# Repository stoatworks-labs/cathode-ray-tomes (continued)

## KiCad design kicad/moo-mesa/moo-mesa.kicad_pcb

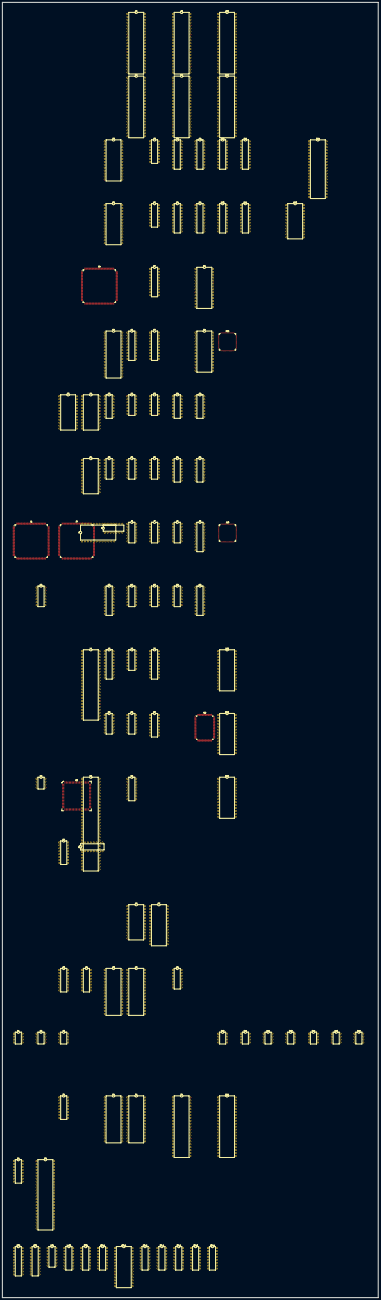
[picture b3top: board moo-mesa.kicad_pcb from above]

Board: 2 copper layers, 326.1 x 1123.8 mm, 109 parts (0 on the bottom side), 698 nets, no tracks yet.

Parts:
A6: HN624116P; DIP-42_W15.24mm
A8, A10: 065A08; DIP-42_W15.24mm
B6: HN624116P; DIP-42_W15.24mm
B8, B10: 065A08; DIP-42_W15.24mm
C5: HM62256BLP; DIP-28_W15.24mm
C7: 74LS157; DIP-16_W7.62mm
C8, C9, C10, C11: 74LS374; DIP-20_W7.62mm
C14: Z80CPU; DIP-40_W15.24mm
D5: MB8464A-10W-15W; DIP-28_W15.24mm
D7: 74LS174; DIP-16_W7.62mm
D8, D9, D10, D11: 74LS374; DIP-20_W7.62mm
D13: YM2151; DIP-24_W15.24mm
E4: 054539; PQFP-160_28x28mm_P0.65mm
E7: PAL16L8; DIP-20_W7.62mm
E9: LH5168D-80L; DIP-28_W15.24mm
F5: 27C020; DIP-32_W15.24mm
F6, F7: 74LS245; DIP-20_W7.62mm
F9: LH5168D-80L; DIP-28_W15.24mm
F10: 053246; TQFP-120_14x14mm_P0.4mm
G3: 051550; DIP-24_W15.24mm
G4: HM6116P-3; DIP-24_W15.24mm
G5: 74LS367; DIP-16_W7.62mm
G6: 74LS04; DIP-14_W7.62mm
G6B, G7B: 74LS245; DIP-20_W7.62mm
G7: 74LS08; DIP-14_W7.62mm
G8, G9: 74LS157; DIP-16_W7.62mm
H4: HM6116P-3; DIP-24_W15.24mm
H5: 74LS21; DIP-14_W7.62mm
H6: 74LS08; DIP-14_W7.62mm
H7: 74LS32; DIP-14_W7.62mm
H8, H9: 74LS157; DIP-16_W7.62mm
J1: 054157; PQFP-160_28x28mm_P0.65mm
J3: 054338; PQFP-160_28x28mm_P0.65mm
J4: HM6116P-3; DIP-24_W15.24mm
J5: 74LS07; DIP-14_W7.62mm
J6: 74LS74; DIP-14_W7.62mm
J7: 74LS32; DIP-14_W7.62mm
J8: 74LS86; DIP-14_W7.62mm
J9: 74LS273; DIP-20_W7.62mm
J10: 053247; TQFP-120_14x14mm_P0.4mm
K2, K8: 74LS04; DIP-14_W7.62mm
K5, K9: 74LS273; DIP-20_W7.62mm
K6: 74LS32; DIP-14_W7.62mm
K7: 74LS74; DIP-14_W7.62mm
L4: DIP-48_W15.24mm
L5, L7: 74LS273; DIP-20_W7.62mm
L6: 74LS04; DIP-14_W7.62mm
L6B: 74LS138; DIP-14_W7.62mm
L10: MB8464A-10W-15W; DIP-28_W15.24mm
L_B6: 74LS157; DIP-16_W7.62mm
M5, M6: 74LS04; DIP-14_W7.62mm
M6B: 74LS138; DIP-16_W7.62mm
M7: 74LS174; DIP-16_W7.62mm
M9: 053251; PQFP-100_14x20mm_P0.65mm
M10: MB8464A-10W-15W; DIP-28_W15.24mm
N2: ER5911; DIP-8_W7.62mm
N3: MC68000FN; PLCC-68
N4: DIP-64_W15.24mm
N6: 74LS175; DIP-16_W7.62mm
N10: MB8464A-10W-15W; DIP-28_W15.24mm
O3, O4: 74LS257; DIP-16_W7.62mm
P6: PAL20L10; DIP-24_W15.24mm
P7: DIP-28_W15.24mm
Q3: 74LS148; DIP-16_W7.62mm
Q4: 74LS174; DIP-16_W7.62mm
Q5, Q6: 27C010; DIP-32_W15.24mm
Q8: 74LS32; DIP-14_W7.62mm
R3_2: 74LS257; DIP-16_W7.62mm
R5_2: HM62256BLP; DIP-28_W15.24mm
S1, S2, S3, S10, S11, S12, S13, S14, S15, S16: KONAMI_005273; DIP-8_W7.62mm
S3_2: 74LS257; DIP-16_W7.62mm
T3: 74LS257; DIP-16_W7.62mm
T5, T6: 27C010; DIP-32_W15.24mm
T8, T10: 065A08; DIP-42_W15.24mm
U1: AD1868R; DIP-16_W7.62mm
U2: 054321; DIP-48_W15.24mm
U7_1, U7_2, U7_3, U7_4: DIP-16_W7.62mm

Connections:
/1.54CLK: E4.28, U1.4, U2.7
/1P_BTN_1: R3_2.2, S1.1, S1.2
/1P_BTN_2: R3_2.5, S1.5, S1.6
/1P_BTN_3: R3_2.11, S10.1, S10.2
/1P_DOWN: O3.14, S3.5, S3.6
/1P_LEFT: O3.2, S2.1, S2.2
/1P_RIGHT: O3.5, S2.5, S2.6
/1P_UP: O3.11, S3.1, S3.2
/2P_BTN_1: R3_2.3, S1.3, S1.4
/2P_BTN_2: R3_2.6, S1.7, S1.8
/2P_BTN_3: R3_2.10, S10.3, S10.4
/2P_DOWN: O3.13, S3.7, S3.8
/2P_LEFT: O3.3, S2.3, S2.4
/2P_RIGHT: O3.6, S2.7, S2.8
/2P_UP: O3.10, S3.3, S3.4
/3P_BTN_1: S11.1, S11.2, T3.2
/3P_BTN_2: S11.5, S11.6, T3.5
/3P_BTN_3: S14.1, S14.2, T3.11
/3P_DOWN: S3_2.14, S13.5, S13.6
/3P_LEFT: S3_2.2, S12.1, S12.2
/3P_RIGHT: S3_2.5, S12.5, S12.6
/3P_START: S14.5, S14.6, T3.14
/3P_UP: S3_2.11, S13.1, S13.2
/4MCLK: D13.24, L4.10
/4P_BTN_1: S11.3, S11.4, T3.3
/4P_BTN_2: S11.7, S11.8, T3.6
/4P_BTN_3: S14.3, S14.4, T3.10
/4P_DOWN: S3_2.13, S13.7, S13.8
/4P_LEFT: S3_2.3, S12.3, S12.4
/4P_RIGHT: S3_2.6, S12.7, S12.8
/4P_START: S14.7, S14.8, T3.13
/4P_UP: S3_2.10, S13.3, S13.4
/ACOL0: J1.149, M9.57
/ACOL1: J1.148, M9.58
/ACOL2: J1.55, M9.59
/ACOL3: J1.56, M9.60
/APAL0: J1.127, M9.61
/APAL1: J1.126, M9.62
/APAL2: J1.125, M9.63
/BCOL0: J1.147, M9.66
/BCOL1: J1.146, M9.67
/BCOL2: J1.57, M9.68
/BCOL3: J1.58, M9.69
/BNK~SCR: J1.64, L6B.11
/BPAL0: J1.122, M9.70
/BPAL1: J1.119, M9.71
/BPAL2: J1.118, M9.72
/BPAL3: J1.117, M9.73
/CI0: J1.154, L7.3
/CI1: J1.153, L7.4
/CI2: J1.51, L7.7
/CI3: J1.52, L7.8
/CI4: J1.143, L7.13
/CI5: J1.142, L7.14
/CI6: J1.141, L7.17
/CI7: J1.138, L7.18
/COIN_1: O4.2, S15.1, S15.2
/COIN_2: O4.5, S15.3, S15.4
/COIN_3: O4.11, S15.5, S15.6
/COIN_4: O4.14, S15.7, S15.8
/COLCS: L6B.14, P7.22
/CRKB: F10.9, N6.3
/CR~CS: J10.9, M6B.13
/DTACK: H5.2, J3.35
/FCOL0: J1.152, L_B6.14
/FCOL1: J1.151, L_B6.11
/FCOL2: J1.53, L_B6.5
/FCOL3: J1.54, L_B6.2
/FPAL0: J1.135, M9.51
/FPAL1: J1.134, M9.52
/FPAL2: J1.133, M9.54
/FPAL3: J1.132, M9.55
/FPAL4: H6.12, J1.137, M9.56
/G5P11: F7.13, G5.11
/G5P13: F7.12, G5.13
/GFXROMA0: T8.10, T10.10
/GFXROMA1: T8.9, T10.9
/GFXROMA2: T8.8, T10.8
/GFXROMA3: T8.7, T10.7
/GFXROMA4: T8.6, T10.6
/GFXROMA5: T8.5, T10.5
/GFXROMA6: T8.4, T10.4
/GFXROMA7: T8.3, T10.3
/GFXROMA8: T8.41, T10.41
/GFXROMA9: T8.40, T10.40
/GFXROMA10: T8.39, T10.39
/GFXROMA11: T8.38, T10.38
/GFXROMA12: T8.37, T10.37
/GFXROMA13: T8.36, T10.36
/GFXROMA14: T8.35, T10.35
/GFXROMA15: T8.34, T10.34
/GFXROMA16: T8.33, T10.33
/GFXROMA17: T8.2, T10.2
/GFXROMA18: T8.1, T10.1
/GFXROMA19: T8.42, T10.42
/GFXROMD0: J1.16, T8.14
/GFXROMD1: J1.17, T8.16
/GFXROMD2: J1.18, T8.18
/GFXROMD3: J1.19, T8.20
/GFXROMD4: J1.9, T8.23
/GFXROMD5: J1.11, T8.25
/GFXROMD6: J1.12, T8.27
/GFXROMD7: J1.13, T8.29
/GFXROMD8: J1.3, T8.15
/GFXROMD9: J1.4, T8.17
/GFXROMD10: J1.5, T8.19
/GFXROMD11: J1.6, T8.21
/GFXROMD12: J1.155, T8.24
/GFXROMD13: J1.156, T8.26
/GFXROMD14: J1.157, T8.28
/GFXROMD15: J1.158, T8.30
/GFXROMD16: J1.44, T10.14
/GFXROMD17: J1.45, T10.16
/GFXROMD18: J1.46, T10.18
/GFXROMD19: J1.47, T10.20
/GFXROMD20: J1.36, T10.23
/GFXROMD21: J1.37, T10.25
/GFXROMD22: J1.38, T10.27
/GFXROMD23: J1.39, T10.29
/GFXROMD24: J1.29, T10.15
/GFXROMD25: J1.31, T10.17
/GFXROMD26: J1.32, T10.19
/GFXROMD27: J1.33, T10.21
/GFXROMD28: J1.23, T10.24
/GFXROMD29: J1.24, T10.26
/GFXROMD30: J1.25, T10.28
/GFXROMD31: J1.26, T10.30
/IOCS: L6B.10, O3.15, R3_2.15, S3_2.15, T3.15
/IOCSB: L6B.9, O4.15
/K051550_CLK: G3.1, N6.11
/LYR_PRIO: J6.12, P6.17
/M16: F10.10, J1.111, J10.10, K5.11, L5.11, M6.8, M9.41, N4.56
/M16B: M6.10, M7.9, N3.15
/MAIN_A1: F7.2, F10.7, G6.1, J1.74, J3.11, J10.7, L4.42, M9.85, N3.32, N4.30, P7.10, Q5.12, Q6.12, R5_2.10, T5.12, T6.12, U2.35
/MAIN_A2: F7.3, F10.6, J1.75, J3.12, J10.6, L4.41, M9.84, N3.33, N4.29, P7.9, Q5.11, Q6.11, R5_2.9, T5.11, T6.11, U2.34
/MAIN_A3: F7.4, J3.13, L4.40, M9.83, N3.34, N4.28, P7.8, Q5.10, Q6.10, R5_2.8, T5.10, T6.10, U2.33
/MAIN_A4: F7.5, J3.14, L4.38, M9.82, N3.35, N4.27, P7.7, Q5.9, Q6.9, R5_2.7, T5.9, T6.9, U2.32
/MAIN_A5: F7.6, J3.15, N3.36, N4.24, P7.6, Q5.8, Q6.8, R5_2.6, T5.8, T6.8
/MAIN_A6: F7.7, J3.16, N3.37, N4.23, Q5.7, Q6.7, R5_2.5, T5.7, T6.7
/MAIN_A7: F7.8, J3.17, N3.38, N4.22, Q5.6, Q6.6, R5_2.4, T5.6, T6.6
/MAIN_A8: F7.9, J3.18, N3.39, N4.21, Q5.5, Q6.5, R5_2.3, T5.5, T6.5
/MAIN_A9: F6.2, J3.19, N3.40, N4.20, Q5.27, Q6.27, R5_2.25, T5.27, T6.27
/MAIN_A10: F6.3, J3.21, N3.41, N4.19, Q5.26, Q6.26, R5_2.24, T5.26, T6.26
/MAIN_A11: F6.4, J3.22, N3.42, N4.17, Q5.23, Q6.23, R5_2.21, T5.23, T6.23
/MAIN_A12: F6.5, J3.23, N3.43, N4.16, Q5.25, Q6.25, R5_2.23, T5.25, T6.25
/MAIN_A13: F6.6, L6B.1, M6B.1, N3.44, N4.15, Q5.4, Q6.4, R5_2.2, T5.4, T6.4
/MAIN_A14: L6B.2, M6B.2, N3.45, N4.14, P6.11, Q5.28, Q6.28, R5_2.26, T5.28, T6.28
/MAIN_A15: M6B.3, N3.46, N4.13, P6.10, Q5.29, Q6.29, R5_2.1, T5.29, T6.29
/MAIN_A16: M5.3, N3.47, N4.12, P6.9, Q5.3, Q6.3, T5.3, T6.3
/MAIN_A17: N3.48, N4.11, P6.8, Q5.2, Q6.2, T5.2, T6.2
/MAIN_A18: N3.49, N4.8, P6.7
/MAIN_A19: N3.50, N4.7, P6.6
/MAIN_A20: N3.51, N4.6, P6.5
/MAIN_A21: N3.53, N4.5, P6.4
/MAIN_A22: N3.54, N4.4, P6.3
/MAIN_A23: N3.55, N4.3, P6.13
/MAIN_D0: G7B.2, J1.76, J3.26, J10.30, L4.13, M9.80, N3.5, N4.31, O3.4, O4.4, P7.11, Q4.3, Q5.13, T5.13, U2.44
/MAIN_D1: G7B.3, J1.77, J3.27, J10.29, L4.14, M9.79, N3.4, N4.32, O3.7, O4.7, P7.12, Q4.4, Q5.14, T5.14, U2.43
/MAIN_D2: G7B.4, J1.78, J3.28, J10.28, L4.15, M9.77, N3.3, N4.33, O3.9, O4.9, P7.13, Q4.6, Q5.15, T5.15, U2.42
/MAIN_D3: G7B.5, J1.79, J3.29, J10.27, L4.16, M9.76, N3.2, N4.35, O3.12, O4.12, P7.15, Q4.11, Q5.17, T5.17, U2.41
/MAIN_D4: G7B.6, J1.82, J3.31, J10.26, L4.18, M9.75, N3.1, N4.36, P7.16, Q4.13, Q5.18, R3_2.4, T5.18, U2.40
/MAIN_D5: G7B.7, J1.83, J3.32, J10.25, L4.19, M9.74, N3.68, N4.37, P7.17, Q4.14, Q5.19, R3_2.7, T5.19, U2.39
/MAIN_D6: G7B.8, J1.84, J3.33, J10.24, L4.20, N3.67, N4.38, P7.18, Q5.20, R3_2.9, T5.20, U2.38
/MAIN_D7: G7B.9, J1.85, J3.34, J10.23, L4.21, N3.66, N4.39, P7.19, Q5.21, R3_2.12, T5.21, U2.37
/MAIN_D8: J1.86, J3.36, J10.22, N3.65, N4.40, N6.4, Q6.13, R5_2.11, S3_2.4, T6.13
/MAIN_D9: J1.87, J3.37, J10.20, N3.64, N4.43, N6.5, Q6.14, R5_2.12, S3_2.7, T6.14
/MAIN_D10: G6B.4, J1.88, J3.38, J10.19, N3.63, N4.44, N6.12, Q6.15, R5_2.13, S3_2.9, T6.15
/MAIN_D11: J1.89, J3.39, J10.18, N3.62, N4.45, N6.13, Q6.17, R5_2.15, S3_2.12, T6.17
/MAIN_D12: G6B.6, J1.91, J3.42, J10.17, N3.61, N4.46, Q6.18, R5_2.16, T3.4, T6.18
/MAIN_D13: G6B.7, J1.92, J3.43, J10.15, N3.60, N4.47, Q6.19, R5_2.17, T3.7, T6.19
/MAIN_D14: G6B.8, J1.93, J3.44, J10.14, N3.59, N4.48, Q6.20, R5_2.18, T3.9, T6.20
/MAIN_D15: J1.94, J3.45, J10.13, N3.58, N4.49, Q6.21, R5_2.19, T3.12, T6.21
/MCLK2: F10.12, J10.12, L6.6
/M~RD: F6.9, G7B.1, J1.95, M6.6, R5_2.22
/OBJDMA: F6.19, F7.19, F10.116, K8.5, Q8.2
/OBJROMA0: A8.10, A10.10, B8.10, B10.10, F10.68
/OBJROMA1: A8.9, A10.9, B8.9, B10.9, F10.69
/OBJROMA2: A8.8, A10.8, B8.8, B10.8, F10.70
/OBJROMA3: A8.7, A10.7, B8.7, B10.7, F10.72
/OBJROMA4: A8.6, A10.6, B8.6, B10.6, F10.73
/OBJROMA5: A8.5, A10.5, B8.5, B10.5, F10.74
/OBJROMA6: A8.4, A10.4, B8.4, B10.4, F10.75
/OBJROMA7: A8.3, A10.3, B8.3, B10.3, F10.77
/OBJROMA8: A8.41, A10.41, B8.41, B10.41, F10.78
/OBJROMA9: A8.40, A10.40, B8.40, B10.40, F10.79
/OBJROMA10: A8.39, A10.39, B8.39, B10.39, F10.80
/OBJROMA11: A8.38, A10.38, B8.38, B10.38, F10.82
/OBJROMA12: A8.37, A10.37, B8.37, B10.37, F10.83
/OBJROMA13: A8.36, A10.36, B8.36, B10.36, F10.84
/OBJROMA14: A8.35, A10.35, B8.35, B10.35, F10.85
/OBJROMA15: A8.34, A10.34, B8.34, B10.34, F10.86
/OBJROMA16: A8.33, A10.33, B8.33, B10.33, F10.87
/OBJROMA17: A8.2, A10.2, B8.2, B10.2, F10.88
/OBJROMA18: A8.1, A10.1, B8.1, B10.1, F10.89
/OBJROMA19: A8.42, A10.42, B8.42, B10.42, F10.90
/OCOL0: J10.32, K9.3
/OCOL1: J10.33, K9.4
/OCOL2: J10.34, K9.7
/OCOL3: J10.35, K9.8
/OCOL4: J10.36, K9.13
/OCOL5: J10.37, K9.14
/OCOL6: J10.38, K9.17
/OCOL7: J10.39, K9.18
/OCOL8: J9.3, J10.40
/OPRI0: J9.4, J10.42
/OPRI1: J9.7, J10.43
/OPRI2: J9.8, J10.44
/OPRI3: J9.13, J10.45
/OPRI4: J9.14, J10.47
/ORAM~WEH: E9.27, H7.11
/ORAM~WEL: F9.27, H7.8
/PAIR~CS: L6B.12, U2.36
/PCM0: E4.34, U2.1
/PCM1: E4.26, U2.2
/PCM2: E4.27, U2.3
/PCU~CS: M6B.9, M9.81
/RAMCS: J3.157, P6.21
/REGCS: J3.158, M6B.10
/REG_WRITE: J7.10, L6B.7
/RES: G3.10, L4.7
/R_A0: A6.30, B6.30, C5.10, E4.132
/R_A1: A6.10, B6.10, C5.9, E4.135
/R_A2: A6.9, B6.9, C5.8, E4.137
/R_A3: A6.8, B6.8, C5.7, E4.141
/R_A4: A6.7, B6.7, C5.6, E4.143
/R_A5: A6.6, B6.6, C5.5, E4.146
/R_A6: A6.5, B6.5, C5.4, E4.148
/R_A7: A6.4, B6.4, C5.3, E4.151
/R_A8: A6.3, B6.3, C5.25, E4.153
/R_A9: A6.41, B6.41, C5.24, E4.157
/R_A10: A6.40, B6.40, C5.21, E4.154
/R_A11: A6.39, B6.39, C5.23, E4.152
/R_A12: A6.38, B6.38, C5.2, E4.149
/R_A13: A6.37, B6.37, C5.26, E4.147
/R_A14: A6.36, B6.36, E4.144
/R_A15: A6.35, B6.35, E4.142
/R_A16: A6.34, B6.34, C5.1, E4.138
/R_A17: A6.33, B6.33, E4.136
/R_A18: A6.2, B6.2, E4.156
/R_A19: A6.1, B6.1, E4.158
/R_A20: A6.42, B6.42, E4.159
/R_D0: A6.14, B6.14, C5.11, E4.128
/R_D1: A6.16, B6.16, C5.12, E4.126
/R_D2: A6.18, B6.18, C5.13, E4.124
/R_D3: A6.20, B6.20, C5.15, E4.122
/R_D4: A6.23, B6.23, C5.16, E4.123
/R_D5: A6.25, B6.25, C5.17, E4.125
/R_D6: A6.27, B6.27, C5.18, E4.127
/R_D7: A6.29, B6.29, C5.19, E4.129
/R/~W: J7.5, K6.5, N3.9
/SCRCS: J1.112, K8.2
/SDON: L6B.13, U2.30
/SERVICE1: S16.1, S16.2
/SHD0: J9.17, J10.48
/SHD1: J9.18, J10.49
/SND~IORQ: C14.20, U2.29
/S~RD: C14.21, D5.22, D13.6, E4.67, E7.2
/S~RST: C14.26, D7.1, D13.3, E4.71, F10.3, J5.1, J5.3, J10.3, N4.59, N6.1, Q4.1
/S~WR: C14.22, D5.27, D13.5, E4.68
/XOBJROMD0: A8.14, D9.3
/XOBJROMD1: A8.16, D9.4
/XOBJROMD2: A8.18, D9.7
/XOBJROMD3: A8.20, D9.8
/XOBJROMD4: A8.23, D9.13
/XOBJROMD5: A8.25, D9.14
/XOBJROMD6: A8.27, D9.17
/XOBJROMD7: A8.29, D9.18
/XOBJROMD8: A8.15, D8.3
/XOBJROMD9: A8.17, D8.4
/XOBJROMD10: A8.19, D8.7
/XOBJROMD11: A8.21, D8.8
/XOBJROMD12: A8.24, D8.13
/XOBJROMD13: A8.26, D8.14
/XOBJROMD14: A8.28, D8.17
/XOBJROMD15: A8.30, D8.18
/XOBJROMD16: B8.14, C9.3
/XOBJROMD17: B8.16, C9.4
/XOBJROMD18: B8.18, C9.7
/XOBJROMD19: B8.20, C9.8
/XOBJROMD20: B8.23, C9.13
/XOBJROMD21: B8.25, C9.14
/XOBJROMD22: B8.27, C9.17
/XOBJROMD23: B8.29, C9.18
/XOBJROMD24: B8.15, C8.3
/XOBJROMD25: B8.17, C8.4
/XOBJROMD26: B8.19, C8.7
/XOBJROMD27: B8.21, C8.8
/XOBJROMD28: B8.24, C8.13
/XOBJROMD29: B8.26, C8.14
/XOBJROMD30: B8.28, C8.17
/XOBJROMD31: B8.30, C8.18
/YOBJROMD0: A10.14, D11.3
/YOBJROMD1: A10.16, D11.4
/YOBJROMD2: A10.18, D11.7
/YOBJROMD3: A10.20, D11.8
/YOBJROMD4: A10.23, D11.13
/YOBJROMD5: A10.25, D11.14
/YOBJROMD6: A10.27, D11.17
/YOBJROMD7: A10.29, D11.18
/YOBJROMD8: A10.15, C11.3
/YOBJROMD9: A10.17, C11.4
/YOBJROMD10: A10.19, C11.7
/YOBJROMD11: A10.21, C11.8
/YOBJROMD12: A10.24, C11.13
/YOBJROMD13: A10.26, C11.14
/YOBJROMD14: A10.28, C11.17
/YOBJROMD15: A10.30, C11.18
/YOBJROMD16: B10.14, D10.3
/YOBJROMD17: B10.16, D10.4
/YOBJROMD18: B10.18, D10.7
/YOBJROMD19: B10.20, D10.8
/YOBJROMD20: B10.23, D10.13
/YOBJROMD21: B10.25, D10.14
/YOBJROMD22: B10.27, D10.17
/YOBJROMD23: B10.29, D10.18
/YOBJROMD24: B10.15, C10.3
/YOBJROMD25: B10.17, C10.4
/YOBJROMD26: B10.19, C10.7
/YOBJROMD27: B10.21, C10.8
/YOBJROMD28: B10.24, C10.13
/YOBJROMD29: B10.26, C10.14
/YOBJROMD30: B10.28, C10.17
/YOBJROMD31: B10.30, C10.18
/colmix/053251/BRIT: H8.5, M9.88
/colmix/053251/COL0: G9.2, M9.19
/colmix/053251/COL1: G9.5, M9.18
/colmix/053251/COL2: G9.11, M9.17
/colmix/053251/COL3: G9.14, M9.16
/colmix/053251/COL4: G8.2, M9.14
/colmix/053251/COL5: G8.5, M9.13
/colmix/053251/COL6: G8.11, M9.12
/colmix/053251/COL7: G8.14, M9.11
/colmix/053251/COL8: H9.2, M9.93
/colmix/053251/COL9: H9.5, M9.92
/colmix/053251/COL10: H9.11, M9.91
/colmix/053251/CRAM~CS: G8.1, G9.1, H8.1, H9.1, K7.9
/colmix/053251/FCOLR0: L_B6.4, M9.47
/colmix/053251/FCOLR1: L_B6.7, M9.48
/colmix/053251/FCOLR2: L_B6.9, M9.49
/colmix/053251/FCOLR3: L_B6.12, M9.50
/colmix/053251/L7P2: G9.3, L7.2
/colmix/053251/L7P5: G9.6, L7.5
/colmix/053251/L7P6: G9.10, L7.6
/colmix/053251/L7P9: G9.13, L7.9
/colmix/053251/L7P12: G8.3, L7.12
/colmix/053251/L7P15: G8.6, L7.15
/colmix/053251/L7P16: G8.10, L7.16
/colmix/053251/L7P19: G8.13, L7.19
/colmix/053251/MCLK2: K7.11, L6.1, L7.11
/colmix/053251/MCOL0: G9.4, L5.3
/colmix/053251/MCOL1: G9.7, L5.4
/colmix/053251/MCOL2: G9.9, L5.7
/colmix/053251/MCOL3: G9.12, L5.8
/colmix/053251/MCOL4: G8.4, L5.13
/colmix/053251/MCOL5: G8.7, L5.14
/colmix/053251/MCOL6: G8.9, L5.17
/colmix/053251/MCOL7: G8.12, L5.18
/colmix/053251/MCOLB0: H6.9, H9.4, K5.3
/colmix/053251/MCOLB1: H9.7, K5.4, L6.9
/colmix/053251/MCOLB2: H9.9, K5.7, L6.10
/colmix/053251/MCOLB4: H8.4, K5.8
/colmix/053251/MCOLB5: H8.7, K5.13
/colmix/053251/MCOLB6: H8.9, K5.14
/colmix/053251/MCOLB7: H8.12, K5.17
/colmix/053251/MCOLB_A: H6.8, K5.18
/colmix/053251/MCOLR0: J3.51, L5.2
/colmix/053251/MCOLR1: J3.52, L5.5
/colmix/053251/MCOLR2: J3.53, L5.6
/colmix/053251/MCOLR3: J3.54, L5.9
/colmix/053251/MCOLR4: J3.55, L5.12
/colmix/053251/MCOLR5: J3.56, L5.15
/colmix/053251/MCOLR6: J3.57, L5.16
/colmix/053251/MCOLR7: J3.58, L5.19
/colmix/053251/MCOLRB0: J3.63, K5.2
/colmix/053251/MCOLRB1: J3.64, K5.5
/colmix/053251/MCOLRB2: J3.65, K5.6
/colmix/053251/MCOLRB3: J3.74, K5.9
/colmix/053251/MCOLRB4: J3.156, K5.12
/colmix/053251/MCOLRB5: J3.46, K5.15
/colmix/053251/MCOLRB6: J3.47, K5.16
/colmix/053251/NCOL: H8.2, M9.89
/colmix/053251/PR01: J9.5, M9.98
/colmix/053251/PR02: J9.6, M9.99
/colmix/053251/PR03: J9.9, M9.100
/colmix/053251/PR04: J9.12, M9.1
/colmix/053251/PR05: J9.15, M9.2
/colmix/053251/SDO0: H8.11, M9.87
/colmix/053251/SDO1: H8.14, M9.86
/colmix/053251/SHDR0: J9.16, M9.95
/colmix/053251/SHDR1: J9.19, M9.96
/colmix/RGB/BOUT0: J3.144, U7_3.14
/colmix/RGB/BOUT1: J3.143, U7_3.13
/colmix/RGB/BOUT2: J3.142, U7_3.12
/colmix/RGB/BOUT3: J3.141, U7_3.10
/colmix/RGB/BOUT4: J3.138, U7_3.9
/colmix/RGB/BOUT5: J3.137, U7_3.8
/colmix/RGB/BOUT6: J3.136, U7_3.7
/colmix/RGB/BOUT7: J3.135, U7_3.6
/colmix/RGB/CBLK0: J3.145, U7_1.5, U7_2.5, U7_3.5, U7_4.5
/colmix/RGB/DBB0: J3.2, J4.9
/colmix/RGB/DBB1: J3.3, J4.10
/colmix/RGB/DBB2: J3.4, J4.11
/colmix/RGB/DBB3: J3.5, J4.13
/colmix/RGB/DBB4: J3.6, J4.14
/colmix/RGB/DBB5: J3.7, J4.15
/colmix/RGB/DBB6: J3.8, J4.16
/colmix/RGB/DBB7: J3.9, J4.17
/colmix/RGB/DBR0: H4.9, J3.86
/colmix/RGB/DBR1: H4.10, J3.87
/colmix/RGB/DBR2: H4.11, J3.88
/colmix/RGB/DBR3: H4.13, J3.89
/colmix/RGB/DBR4: H4.14, J3.91
/colmix/RGB/DBR5: H4.15, J3.92
/colmix/RGB/DBR6: H4.16, J3.93
/colmix/RGB/DBR7: H4.17, J3.94
/colmix/RGB/GOUT0: J3.134, U7_2.14
/colmix/RGB/GOUT1: J3.133, U7_2.13
/colmix/RGB/GOUT2: J3.132, U7_2.12
/colmix/RGB/GOUT3: J3.131, U7_2.10
/colmix/RGB/GOUT4: J3.129, U7_2.9
/colmix/RGB/GOUT5: J3.128, U7_2.8
/colmix/RGB/GOUT6: J3.127, U7_2.7
/colmix/RGB/GOUT7: J3.126, U7_2.6
/colmix/RGB/OEB: J3.102, J4.20
/colmix/RGB/OER: H4.20, J3.96
/colmix/RGB/RAB0: H4.8, J3.68, J4.8
/colmix/RGB/RAB1: H4.7, J3.69, J4.7
/colmix/RGB/RAB2: H4.6, J3.71, J4.6
/colmix/RGB/RAB3: H4.5, J3.72, J4.5
/colmix/RGB/RAB4: H4.4, J3.73, J4.4
/colmix/RGB/RAB5: H4.3, J3.76, J4.3
/colmix/RGB/RAB6: H4.2, J3.77, J4.2
/colmix/RGB/RAB7: H4.1, J3.78, J4.1
/colmix/RGB/RAB8: H4.23, J3.79, J4.23
/colmix/RGB/RAB9: H4.22, J3.82, J4.22
/colmix/RGB/RAB10: H4.19, J3.83, J4.19
/colmix/RGB/ROUT0: J3.125, U7_1.14
/colmix/RGB/ROUT1: J3.124, U7_1.13
/colmix/RGB/ROUT2: J3.123, U7_1.12
/colmix/RGB/ROUT3: J3.122, U7_1.10
/colmix/RGB/ROUT4: J3.119, U7_1.9
/colmix/RGB/ROUT5: J3.118, U7_1.8
/colmix/RGB/ROUT6: J3.117, U7_1.7
/colmix/RGB/ROUT7: J3.116, U7_1.6
/colmix/RGB/WEB: J3.101, J4.21
/colmix/RGB/WER: H4.21, J3.95
/io_cabinet/EE_~BUSY: N2.7, O4.6
/io_cabinet/I1P_START: R3_2.14, S10.5
/io_cabinet/I2P_START: R3_2.13, S10.7
/io_cabinet/K51550_SI: G3.16, Q4.10
/io_cabinet/PSACA1: M6.2, O3.1, O4.1, R3_2.1, S3_2.1, T3.1
/main/BDS: G7.3, K6.2, L6B.5
/main/HALT: J5.2, N3.19
/main/INT1: L4.34, Q3.1
/main/IPL0: N3.27, Q3.9
/main/IPL1: N3.26, Q3.7
/main/IPL2: N3.25, Q3.6
/main/IRQ: G6B.5, Q3.2
/main/OBJ_REG_SEL: K6.1, M6B.7
/main/ORAM_L: H7.3, H7.10, Q8.5
/main/ORAM_U: H7.6, H7.12, Q8.9
/main/ORAM~WE: H6.4, H7.9, H7.13, P6.19
/main/PALE: L6B.4, M6B.4, P6.22
/main/PRE_~DTACK: K8.1, K8.9, P6.18
/main/RST: J5.4, N3.20
/main/R/W: H7.1, H7.4, K6.6, L4.37, M6.5, P6.2
/main/VPA: N3.23, P6.20
/main/~AS: K2.13, M6B.5, N3.6, N4.1, P6.1
/main/~BGACK: N3.12, N4.53
/main/~BG: N3.11, N4.52
/main/~BR: N3.13, N4.51
/main/~DTACK: H5.6, N3.10, N4.61
/main/~IPL0: N4.60, Q3.13
/main/~OE1: P6.14, Q5.24, Q6.24
/main/~OE2: P6.15, T5.24, T6.24
/main/~WEH: Q8.8, R5_2.27
/objects/CLKOBJ': C8.11, C9.11, C10.11, C11.11, D8.11, D9.11, D10.11, D11.11, F10.66
/objects/EA1: E9.9, F7.18, F9.9, F10.112
/objects/EA2: E9.8, F7.17, F9.8, F10.110
/objects/EA3: E9.7, F7.16, F9.7, F10.109
/objects/EA4: E9.6, F7.15, F9.6, F10.108
/objects/EA5: E9.10, F7.14, F9.10, F10.107
/objects/EN0: E9.5, F7.11, F9.5, F10.105
/objects/EN1: E9.4, F6.18, F9.4, F10.104
/objects/EN2: E9.3, F6.17, F9.3, F10.103
/objects/EN3: E9.25, F6.16, F9.25, F10.102
/objects/EN4: E9.24, F6.15, F9.24, F10.100
/objects/EN5: E9.21, F6.14, F9.21, F10.99
/objects/EN6: E9.23, F6.13, F9.23, F10.98
/objects/EN7: E9.2, F6.12, F9.2, F10.97
/objects/G2D0: F10.32, J10.119
/objects/G2D1: F10.33, J10.118
/objects/G2D2: F10.34, J10.117
/objects/G2D3: F10.35, J10.116
/objects/G2D4: F10.36, J10.115
/objects/G2D5: F10.37, J10.114
/objects/G2D6: F10.38, J10.113
/objects/G2D7: F10.39, J10.112
/objects/G2D8: F10.40, J10.110
/objects/G2D9: F10.42, J10.109
/objects/G2D10: F10.43, J10.108
/objects/G2D11: F10.44, J10.107
/objects/G2D12: F10.45, J10.105
/objects/G2D13: F10.47, J10.104
/objects/G2D14: F10.48, J10.103
/objects/G2D15: F10.49, J10.102
/objects/G2D16: F10.50, J10.100
/objects/G2D17: F10.52, J10.99
/objects/G2D18: F10.53, J10.98
/objects/G2D19: F10.54, J10.97
/objects/G2D20: F10.55, J10.96
/objects/G2D21: F10.56, J10.95
/objects/LUTD0: F9.11, F10.30, G6B.18
/objects/LUTD1: F9.12, F10.29, G6B.17
/objects/LUTD2: F9.13, F10.28, G6B.16
/objects/LUTD3: F9.15, F10.27, G6B.15
/objects/LUTD4: F9.16, F10.26, G6B.14
/objects/LUTD5: F9.17, F10.25
/objects/LUTD6: F9.18, F10.24
/objects/LUTD7: F9.19, F10.23
/objects/LUTD8: E9.11, F10.22, G7B.18
/objects/LUTD9: E9.12, F10.20, G7B.17
/objects/LUTD10: E9.13, F10.19, G7B.16
/objects/LUTD11: E9.15, F10.18, G7B.15
/objects/LUTD12: E9.16, F10.17, G7B.14
/objects/LUTD13: E9.17, F10.15, G7B.13
/objects/LUTD14: E9.18, F10.14, G7B.12
/objects/LUTD15: E9.19, F10.13, G7B.11
/objects/OBJROMD'0: C9.2, D9.2, D10.2, D11.2, J10.72
/objects/OBJROMD'1: C9.5, D9.5, D10.5, D11.5, J10.73
/objects/OBJROMD'2: C9.6, D9.6, D10.6, D11.6, J10.74
/objects/OBJROMD'3: C9.9, D9.9, D10.9, D11.9, J10.75
/objects/OBJROMD'4: C9.12, D9.12, D10.12, D11.12, J10.77
/objects/OBJROMD'5: C9.15, D9.15, D10.15, D11.15, J10.78
/objects/OBJROMD'6: C9.16, D9.16, D10.16, D11.16, J10.79
/objects/OBJROMD'7: C9.19, D9.19, D10.19, D11.19, J10.80
/objects/OBJROMD'8: C8.2, C10.2, C11.2, D8.2, J10.82
/objects/OBJROMD'9: C8.5, C10.5, C11.5, D8.5, J10.83
/objects/OBJROMD'10: C8.6, C10.6, C11.6, D8.6, J10.84
/objects/OBJROMD'11: C8.9, C10.9, C11.9, D8.9, J10.85
/objects/OBJROMD'12: C8.12, C10.12, C11.12, D8.12, J10.86
/objects/OBJROMD'13: C8.15, C10.15, C11.15, D8.15, J10.87
/objects/OBJROMD'14: C8.16, C10.16, C11.16, D8.16, J10.88
/objects/OBJROMD'15: C8.19, C10.19, C11.19, D8.19, J10.89
/objects/~EDE: E9.22, F9.22, F10.114
/objects/~HSYNC: F10.8, J10.8
/objects/~SET0: C8.1, C9.1, F10.62, J10.90
/objects/~SET1: D8.1, D9.1, F10.63, J10.92
/objects/~SET2: C10.1, D10.1, F10.64, J10.93
/objects/~SET3: C11.1, D11.1, F10.65, J10.94
/scroll/SCRAMA0: L10.10, M10.10, N10.10
/scroll/SCRAMA1: L10.9, M10.9, N10.9
/scroll/SCRAMA2: L10.8, M10.8, N10.8
/scroll/SCRAMA3: L10.7, M10.7, N10.7
/scroll/SCRAMA4: L10.6, M10.6, N10.6
/scroll/SCRAMA5: L10.5, M10.5, N10.5
/scroll/SCRAMA6: L10.4, M10.4, N10.4
/scroll/SCRAMA7: L10.3, M10.3, N10.3
/scroll/SCRAMA8: L10.25, M10.25, N10.25
/scroll/SCRAMA9: L10.24, M10.24, N10.24
/scroll/SCRAMA10: L10.21, M10.21, N10.21
/scroll/SCRAMA11: L10.23, M10.23, N10.23
/scroll/SCRAMA12: L10.2, M10.2, N10.2
/scroll/VD0: G4.9, L10.11
/scroll/VD1: G4.8, L10.12
/scroll/VD2: G4.7, L10.13
/scroll/VD3: G4.6, L10.15
/scroll/VD4: G4.5, L10.16
/scroll/VD5: G4.4, L10.17
/scroll/VD6: G4.3, L10.18
/scroll/VD7: G4.2, L10.19
/scroll/VD12: G4.23, N10.16
/scroll/VD13: G4.22, N10.17
/scroll/VD14: G4.21, N10.18
/scroll/VD15: G4.19, N10.19
/scroll/VD17: G4.17, M10.12
/scroll/VD18: G4.16, M10.13
/scroll/VD19: G4.15, M10.15
/scroll/VD20: G4.14, M10.16
/scroll/VD21: G4.13, M10.17
/scroll/VD23: G4.11, M10.19
/sound/054986A/DL: U1.3, U2.9
/sound/054986A/DR: U1.5, U2.11
/sound/054986A/GND: U2.6, U2.27, U2.28
/sound/054986A/LL: U1.2, U1.6, U2.10
/sound/054986A/VSS: U1.7, U1.12
/sound/AUX1: D13.21, E4.39
/sound/GND: C5.14, E7.10
/sound/RAMR~W: C5.27, E4.107
/sound/RAM~CE: C5.20, E4.109
/sound/RAM~OE: C5.22, E4.108
/sound/ROM~CE: B6.11, E4.133
/sound/ROM~OE: B6.13, E4.131
/sound/SBANK0: C7.3, D7.2
/sound/SBANK1: C7.6, D7.5
/sound/SBANK2: C7.10, D7.7
/sound/SBANK3: C7.13, D7.10
/sound/SH1: D13.20, E4.37
/sound/SH2: D13.19, E4.36
/sound/SND_A0: C14.30, D5.10, D13.4, E4.52, F5.12
/sound/SND_A1: C14.31, D5.9, E4.51, F5.11
/sound/SND_A2: C14.32, D5.8, E4.49, F5.10
/sound/SND_A3: C14.33, D5.7, E4.48, F5.9
/sound/SND_A4: C14.34, D5.6, E4.47, F5.8
/sound/SND_A5: C14.35, D5.5, E4.46, F5.7
/sound/SND_A6: C14.36, D5.4, E4.45, F5.6
/sound/SND_A7: C14.37, D5.3, E4.44, F5.5
/sound/SND_A8: C14.38, D5.25, F5.27
/sound/SND_A9: C14.39, D5.24, E4.42, F5.26
/sound/SND_A10: C14.40, D5.21, E7.11, F5.23
/sound/SND_A11: C14.1, D5.23, E7.9, F5.25
/sound/SND_A12: C14.2, D5.2, E7.8, F5.4
/sound/SND_A13: C14.3, E7.7, F5.28
/sound/SND_A14: C14.4, E7.6
/sound/SND_A15: C7.1, C14.5, E7.5
/sound/SND_D0: C14.14, D5.11, D7.3, D13.10, E4.9, F5.13
/sound/SND_D1: C14.15, D5.12, D7.4, D13.12, E4.8, F5.14
/sound/SND_D2: C14.12, D5.13, D7.6, D13.13, E4.7, F5.15
/sound/SND_D3: C14.8, D5.15, D7.11, D13.14, E4.6, F5.17
/sound/SND_D4: C14.7, D5.16, D7.13, D13.15, E4.5, F5.18
/sound/SND_D5: C14.9, D5.17, D7.14, D13.16, E4.4, F5.19
/sound/SND_D6: C14.10, D5.18, D13.17, E4.3, F5.20
/sound/SND_D7: C14.13, D5.19, D13.18, E4.2, F5.21
/sound/SND~PAL8: E7.12, U2.24
/sound/SO~CLK: D13.23, E4.38
/sound/S~M1: C14.27, E7.1
/sound/S~MREQ: C14.19, E7.4
/sound/S~RFSH: C14.28, E7.3
/sound/~FM: D13.7, E7.16
/sound/~IRQ: D13.2, G6.11
/sound/~NMI_CLR: D7.12, G6B.10
/sound/~NMI: C14.17, G6B.9
/sound/~PCM: E4.69, E7.17
/sound/~SBANK_WR: D7.9, E7.14
/sound/~SRAM: D5.20, E7.18
/sound/~SROM: E7.19, F5.24
/~CE: G6B.19, G7B.19, Q8.3
/~HSYNC: J1.113, L4.29
/~INT: C14.16, U2.8
/~LDS: F10.4, G7.1, H7.2, J1.97, J3.98, J7.4, J10.4, N3.8, N4.63
/~M6: J9.11, K8.3, K9.11
/~REG: F10.2, H6.5, J10.2, M6B.14
/~SDON: N2.4, O4.3
/~UDS: F10.5, G7.2, H7.5, J1.96, J3.99, J7.9, J10.5, N3.7, N4.62
GND: G5.8, G7.7, H5.7, H6.7, H7.7, J5.7, J6.7, J7.7, J8.7, J9.10, K2.7, K5.10, K6.7, K7.7, K8.7, K9.10, L5.10, L6.7, L6B.8, L7.10, M5.7, M6.7, M6B.8, M7.8, N3.16, N3.17, N3.56, N3.57, N6.8, Q3.8, Q4.8, Q5.16, Q6.16, Q8.7, T5.16, T6.16
unnamed: C7.4, F5.29
unnamed: C7.7, F5.3
unnamed: C7.9, F5.2
unnamed: C7.12, F5.30
unnamed: G5.2, L4.25
unnamed: G5.15, G6B.3, K8.6
unnamed: G6.2, M6.1
unnamed: G6.3, L6.8
unnamed: G6.4, H6.10
unnamed: G6.10, G6B.11
unnamed: H5.5, K8.10
unnamed: H6.6, Q8.1
unnamed: H6.13, J8.3
unnamed: J6.3, J6.11, K8.4
unnamed: J6.2, K7.5
unnamed: H5.4, J6.5
unnamed: J6.4, J6.10, K2.12, K7.4, M7.1
unnamed: J6.9, K7.2
unnamed: J8.2, L6.2
unnamed: J9.2, M9.21
unnamed: K7.12, Q8.11
unnamed: K9.2, M9.4
unnamed: K9.5, M9.5
unnamed: K9.6, M9.6
unnamed: K9.9, M9.7
unnamed: K9.12, M9.8
unnamed: K9.15, M9.9
unnamed: K9.16, M9.10
unnamed: K9.19, M9.20
unnamed: L4.8, M6.13
unnamed: L4.9, L6.5
unnamed: L6B.3, Q8.13
unnamed: L6B.6, Q8.12
unnamed: H6.11, L_B6.1
unnamed: M6.9, M6.11, M6.12
unnamed: M5.4, M6B.6
unnamed: M7.6, M7.10
unnamed: M7.11, M7.12
unnamed: M7.13, M7.15
unnamed: K8.8, M7.14
unnamed: K8.11, M7.7
unnamed: N2.2, Q4.7
unnamed: N2.1, Q4.5
unnamed: N2.3, Q4.2
unnamed: K6.3, N4.54
unnamed: K6.4, N4.64
unnamed: J7.8, N6.9
unnamed: J8.1, N6.7
unnamed: P6.16, Q8.4, Q8.10
unnamed: H5.1, P6.23
unnamed: J7.6, Q4.9
VCC: A6.22, A8.22, A8.32, A10.22, A10.32, B6.22, B8.22, B8.32, B10.22, B10.32, C5.28, C14.11, C14.24, D5.26, D5.28, D13.22, E4.20, E4.40, E4.56, E4.60, E4.73, E4.80, E4.100, E4.120, E4.140, E4.160, E7.20, E9.26, E9.28, F5.1, F5.31, F5.32, F6.1, F7.1, F9.26, F9.28, F10.16, F10.46, F10.59, F10.60, F10.76, F10.106, F10.120, G4.20, G4.24, G5.16, G6B.1, G6B.13, G7.14, H4.24, H5.14, H6.14, H7.14, H8.3, H9.3, H9.6, H9.10, J1.20, J1.40, J1.60, J1.80, J1.100, J1.106, J1.107, J1.108, J1.116, J1.120, J1.123, J1.124, J1.128, J1.129, J1.131, J1.140, J1.159, J1.160, J3.20, J3.40, J3.60, J3.80, J3.100, J3.120, J3.140, J3.160, J4.24, J5.14, J6.1, J6.13, J6.14, J7.14, J8.14, J9.1, J9.20, J10.16, J10.46, J10.60, J10.70, J10.76, J10.106, J10.120, K2.14, K5.1, K5.20, K6.14, K7.1, K7.10, K7.13, K7.14, K8.14, K9.1, K9.20, L4.3, L4.4, L4.17, L4.39, L5.1, L5.20, L6.14, L7.1, L7.20, L10.26, L10.28, M5.14, M6.14, M6B.16, M7.16, M9.3, M9.28, M9.53, M9.78, M9.97, M10.26, M10.28, N2.8, N3.14, N3.24, N3.52, N4.9, N4.26, N4.41, N4.58, N6.16, N10.26, N10.28, O4.10, P6.24, P7.28, Q3.3, Q3.4, Q3.10, Q3.11, Q3.12, Q3.16, Q4.16, Q5.1, Q5.31, Q5.32, Q6.1, Q6.31, Q6.32, Q8.14, R5_2.28, T5.1, T5.31, T5.32, T6.1, T6.31, T6.32, T8.22, T8.31, T10.22, T10.31, U7_1.15, U7_2.15, U7_3.3, U7_3.15, U7_4.2, U7_4.15
VSS: A6.12, A6.31, A6.32, A8.11, A8.12, A8.13, A8.31, A10.11, A10.12, A10.13, A10.31, B6.12, B6.31, B6.32, B8.11, B8.12, B8.13, B8.31, B10.11, B10.12, B10.13, B10.31, C7.5, C7.11, C7.14, C7.15, C14.29, D5.14, D13.1, D13.11, E4.1, E4.10, E4.30, E4.41, E4.50, E4.57, E4.59, E4.61, E4.62, E4.65, E4.66, E4.70, E4.72, E4.74, E4.81, E4.90, E4.110, E4.121, E4.130, E4.139, E4.150, E9.14, E9.20, F5.16, F5.22, F9.14, F9.20, F10.91, F10.101, F10.111, F10.117, F10.118, F10.119, G3.13, G3.14, G3.15, G4.1, G4.10, G4.12, G4.18, G5.1, G5.12, G5.14, G6B.2, G6B.12, G8.15, G9.15, H4.12, H4.18, H8.6, H8.10, H8.13, H8.15, H9.15, J1.1, J1.7, J1.8, J1.10, J1.14, J1.15, J1.21, J1.22, J1.27, J1.28, J1.30, J1.34, J1.35, J1.41, J1.42, J1.43, J1.48, J1.49, J1.50, J1.59, J1.70, J1.81, J1.90, J1.110, J1.121, J1.130, J1.139, J1.150, J3.1, J3.10, J3.24, J3.25, J3.30, J3.41, J3.50, J3.59, J3.66, J3.67, J3.70, J3.81, J3.90, J3.105, J3.110, J3.115, J3.121, J3.130, J3.139, J3.150, J4.12, J4.18, J10.1, J10.11, J10.21, J10.31, J10.41, J10.51, J10.61, J10.62, J10.63, J10.64, J10.65, J10.66, J10.67, J10.68, J10.69, J10.71, J10.81, J10.91, J10.101, J10.111, L4.6, L4.22, L4.23, L4.28, L4.43, L10.14, L_B6.3, L_B6.6, L_B6.10, L_B6.13, L_B6.15, M9.15, M9.22, M9.23, M9.24, M9.25, M9.27, M9.29, M9.30, M9.31, M9.32, M9.33, M9.34, M9.35, M9.36, M9.37, M9.38, M9.39, M9.40, M9.42, M9.43, M9.44, M9.45, M9.46, M9.65, M9.90, M9.94, M10.14, M10.20, N2.5, N2.6, N4.2, N4.10, N4.18, N4.25, N4.34, N4.42, N4.50, N4.55, N4.57, N10.14, P6.12, P7.14, P7.20, Q3.5, Q5.22, Q6.22, R5_2.14, R5_2.20, T5.22, T6.22, T8.11, T8.12, T8.13, T8.32, T10.11, T10.12, T10.13, T10.32, U7_1.1, U7_1.11, U7_2.1, U7_2.11, U7_3.1, U7_3.11, U7_4.1, U7_4.11
